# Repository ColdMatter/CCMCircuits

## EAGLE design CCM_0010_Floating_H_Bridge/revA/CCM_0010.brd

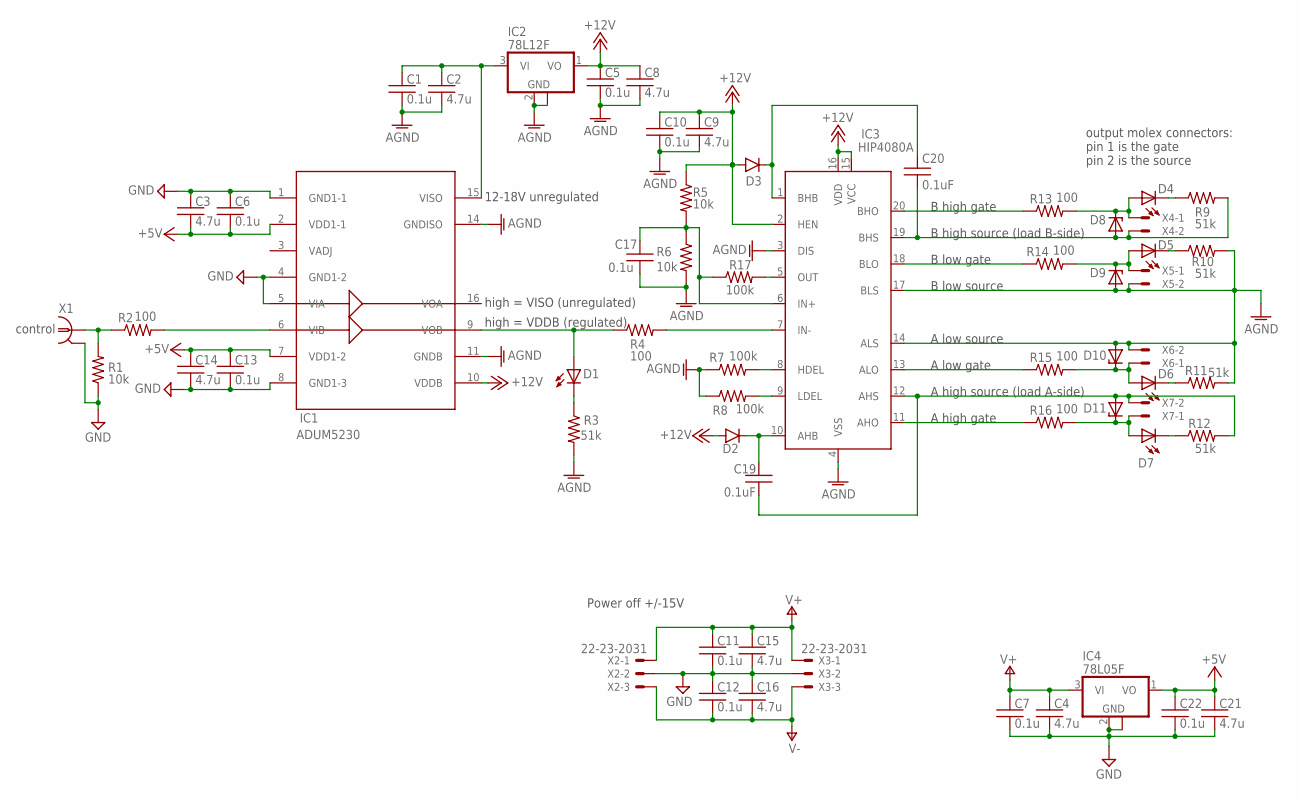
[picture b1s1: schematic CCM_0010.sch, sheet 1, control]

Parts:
C1, C5, C6, C7, C10, C11, C12, C13, C17, C22: 0.1u; 0603
C2, C3, C4, C8, C9, C14, C15, C16, C21: 4.7u; 0603
C19, C20: 0.1uF; 0603
D1, D4, D5, D6, D7: LED0603
D2, D3: DIODESOT23; SOT23-3
D8, D9, D10, D11: ZENER-DIODESOT23; SOT23
IC1: ADUM5230; SO16W
IC2: 78L12F; SOT89
IC3: HIP4080A; SO20W
IC4: 78L05F; SOT89
R1, R5, R6: 10k; 0603
R2, R4, R13, R14, R15, R16: 100; 0603
R3, R9, R10, R11, R12: 51k; 0603
R7, R8, R17: 100k; 0603
X1: 1-227161-0; AMP_227161
X2, X3: 22-23-2031
X4, X5, X6, X7: 22-23-2021

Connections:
+5V: C3.2, C6.2, C13.1, C14.1, C21.1, C22.1, IC1.2 (VDD1-1), IC1.7 (VDD1-2), IC4.1 (VO)
+12V: C5.1, C8.1, C9.1, C10.1, D2.1 (A), D3.1 (A), IC1.10 (VDDB), IC2.1 (VO), IC3.2 (HEN), IC3.15 (VCC), IC3.16 (VDD), R5.1
AGND: C1.2, C2.2, C5.2, C8.2, C9.2, C10.2, C17.2, D9.1 (A), D10.1 (A), IC1.11 (GNDB), IC1.14 (GNDISO), IC2.2 (GND), IC2.2@1 (GND), IC3.3 (DIS), IC3.4 (VSS), IC3.14 (ALS), IC3.17 (BLS), R3.2, R6.2, R7.1, R8.1, R10.2, R11.2, X5.2, X6.2
GND: C3.1, C4.2, C6.1, C7.2, C11.2, C12.1, C13.2, C14.2, C15.2, C16.1, C21.2, C22.2, IC1.1 (GND1-1), IC1.4 (GND1-2), IC1.5 (VIA), IC1.8 (GND1-3), IC4.2 (GND), IC4.2@1 (GND), R1.1, X1.2, X2.2, X3.2
unnamed: D1.C, R3.1
unnamed: D4.C, R9.1
unnamed: D5.C, R10.1
unnamed: IC3.20 (BHO), R13.1
unnamed: D5.A, D9.3 (C), R14.2, X5.1
unnamed: D6.C, R11.1
unnamed: D4.A, D8.3 (C), R13.2, X4.1
unnamed: D1.A, IC1.9 (VOB), R4.1
unnamed: D7.C, R12.1
unnamed: C1.1, C2.1, IC1.15 (VISO), IC2.3 (VI)
unnamed: IC3.11 (AHO), R16.1
unnamed: IC3.13 (ALO), R15.1
unnamed: IC3.7 (IN-), R4.2
unnamed: IC3.9 (LDEL), R8.2
unnamed: C20.2, D3.3 (C), IC3.1 (BHB)
unnamed: C20.1, D8.1 (A), IC3.19 (BHS), R9.2, X4.2
unnamed: IC3.18 (BLO), R14.1
unnamed: IC3.5 (OUT), R17.2
unnamed: C19.1, D11.1 (A), IC3.12 (AHS), R12.2, X7.2
unnamed: D7.A, D11.3 (C), R16.2, X7.1
unnamed: C19.2, D2.3 (C), IC3.10 (AHB)
unnamed: IC3.8 (HDEL), R7.2
unnamed: D6.A, D10.3 (C), R15.2, X6.1
unnamed: R1.2, R2.1, X1.1
unnamed: C17.1, IC3.6 (IN+), R5.2, R6.1, R17.1
unnamed: IC1.6 (VIB), R2.2
V+: C4.1, C7.1, C11.1, C15.1, IC4.3 (VI), X2.1, X3.1
V-: C12.2, C16.2, X2.3, X3.3

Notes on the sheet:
B high source (load B-side)
B high gate
B low gate
B low source
A high gate
A high source (load A-side)
A low gate
A low source
control
12-18V unregulated
high = VISO (unregulated)
high = VDDB (regulated)
Power off +/-15V
output molex connectors: pin 1 is the gate pin 2 is the source

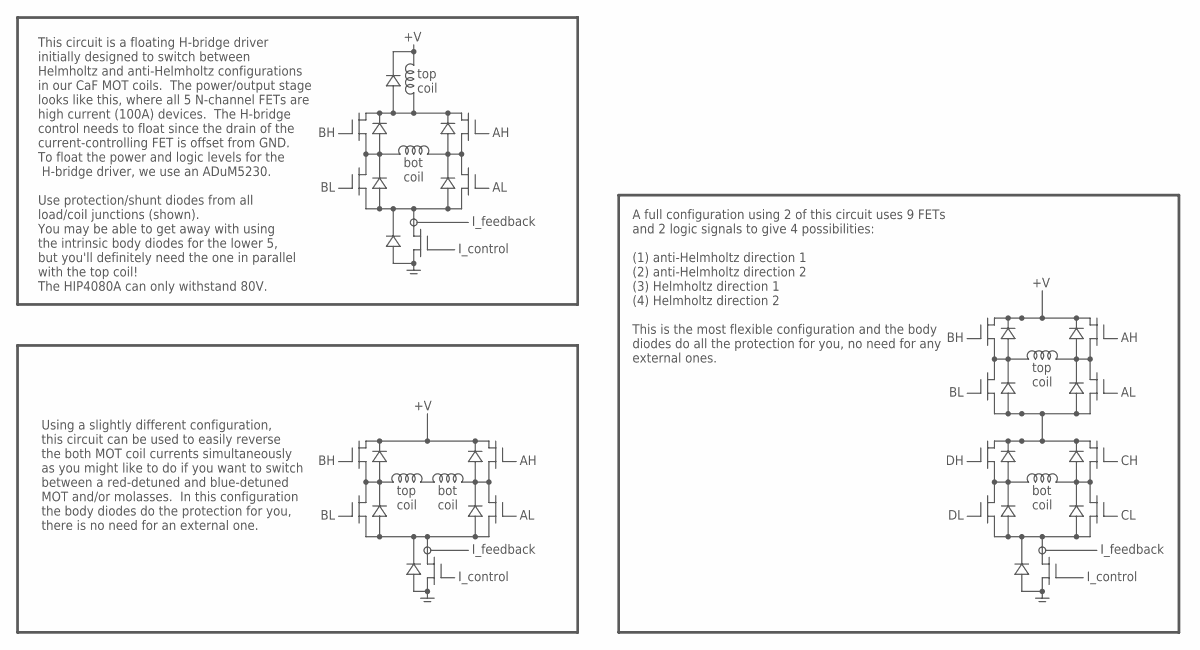
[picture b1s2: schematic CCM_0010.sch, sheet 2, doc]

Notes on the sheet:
I_control
top coil
bot coil
This circuit is a floating H-bridge driver initially designed to switch between Helmholtz and anti-Helmholtz configurations in our CaF MOT coils. The power/output stage looks like this, where all 5 N-channel FETs are high current (100A) devices. The H-bridge control needs to float since the drain o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
I_feedback
Using a slightly different configuration, this circuit can be used to easily reverse the both MOT coil currents simultaneously as you might like to do if you want to switch between a red-detuned and blue-detuned MOT and/or molasses. In this configuration the body diodes do the protection for you, t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
A full configuration using 2 of this circuit uses 9 FETs and 2 logic signals to give 4 possibilities: (1) anti-Helmholtz direction 1 (2) anti-Helmholtz direction 2 (3) Helmholtz direction 1 (4) Helmholtz direction 2 This is the most flexible configuration and the body diodes do all the protection f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

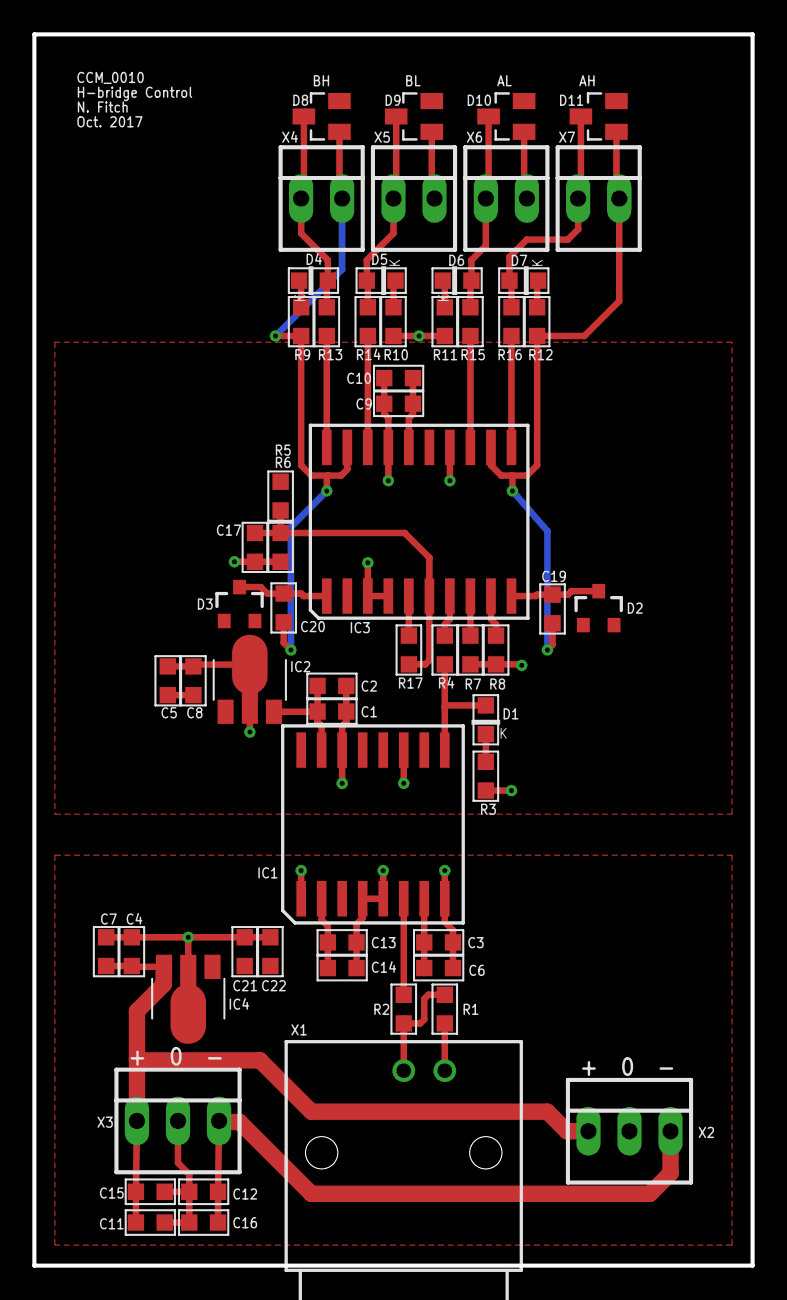
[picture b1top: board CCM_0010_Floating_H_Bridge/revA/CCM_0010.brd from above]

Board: 2 copper layers, 44.5 x 76.2 mm, 60 parts (0 on the bottom side), 32 nets.

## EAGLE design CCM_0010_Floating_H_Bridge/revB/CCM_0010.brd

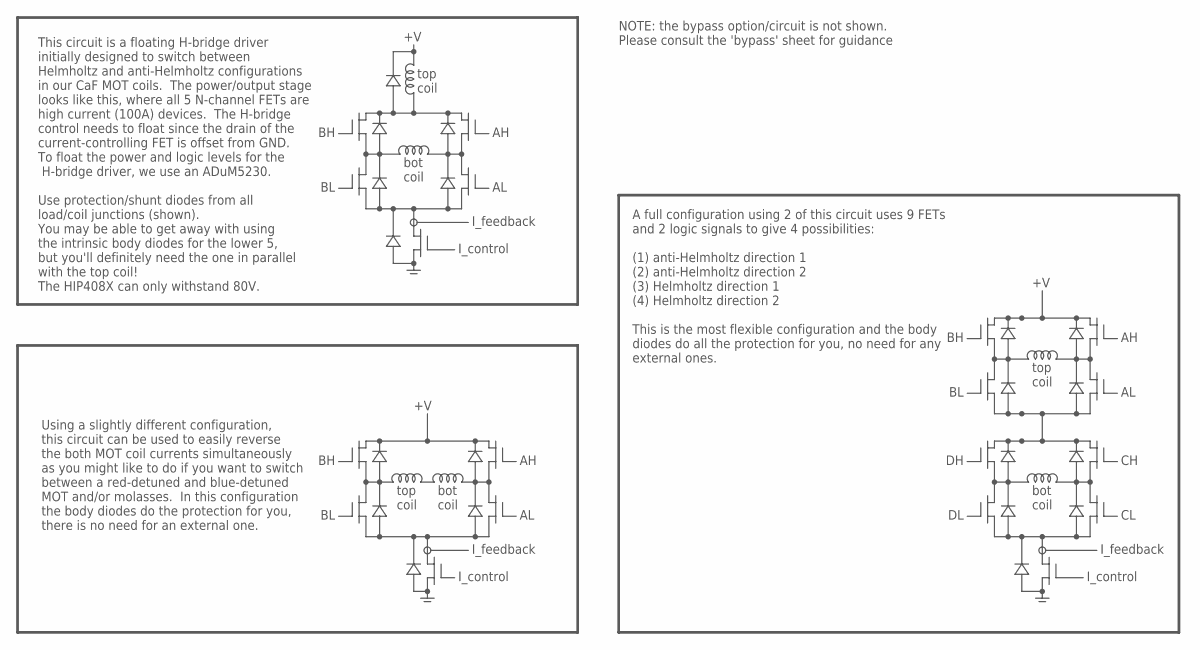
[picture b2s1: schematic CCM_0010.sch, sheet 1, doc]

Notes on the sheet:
I_control
top coil
bot coil
This circuit is a floating H-bridge driver initially designed to switch between Helmholtz and anti-Helmholtz configurations in our CaF MOT coils. The power/output stage looks like this, where all 5 N-channel FETs are high current (100A) devices. The H-bridge control needs to float since the drain o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
I_feedback
Using a slightly different configuration, this circuit can be used to easily reverse the both MOT coil currents simultaneously as you might like to do if you want to switch between a red-detuned and blue-detuned MOT and/or molasses. In this configuration the body diodes do the protection for you, t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
A full configuration using 2 of this circuit uses 9 FETs and 2 logic signals to give 4 possibilities: (1) anti-Helmholtz direction 1 (2) anti-Helmholtz direction 2 (3) Helmholtz direction 1 (4) Helmholtz direction 2 This is the most flexible configuration and the body diodes do all the protection f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
NOTE: the bypass option/circuit is not shown. Please consult the 'bypass' sheet for guidance

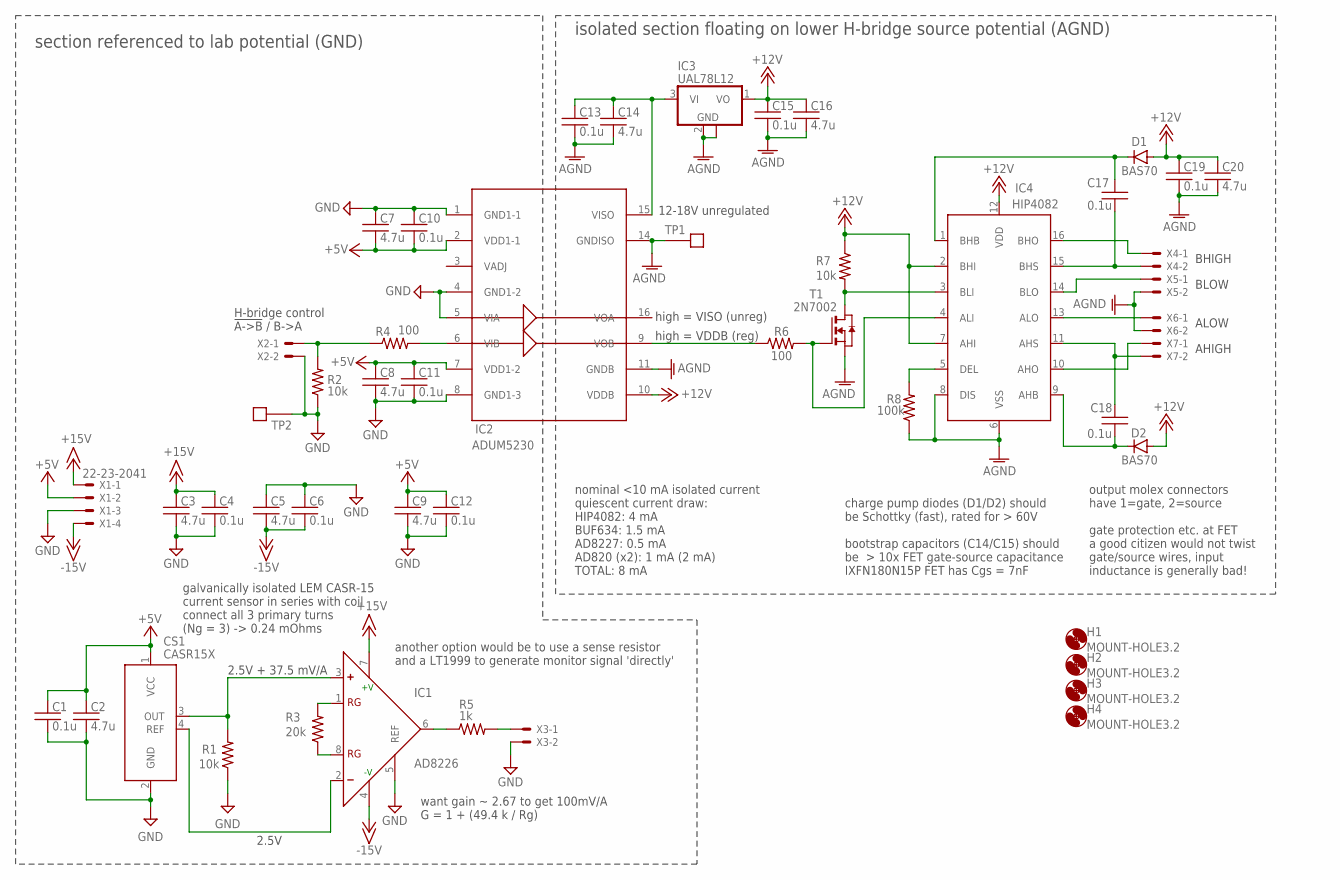
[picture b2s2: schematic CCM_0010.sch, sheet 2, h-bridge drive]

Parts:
C1, C4, C6, C10, C11, C12, C13, C15, C17, C18, C19: 0.1u; 0603
C2, C3, C5, C7, C8, C9, C14, C16, C20: 4.7u; 0603
CS1: CASR15X; 22-23-2041
D1, D2: BAS70; SOT23-3
H1, H2, H3, H4: MOUNT-HOLE3.2; 3,2
IC1: AD8226; SO8
IC2: ADUM5230; SO16W
IC3: UAL78L12; SOT89
IC4: HIP4082; SO16
R1, R2, R7: 10k; 0603
R3: 20k; 0603
R4, R6: 100; 0603
R5: 1k; 0603
R8: 100k; 0603
T1: 2N7002; SOT-23
TP1, TP2: TESTPOINT
X1: 22-23-2041
X2, X3, X4, X5, X6, X7: 22-23-2021

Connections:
+5V: C1.1, C2.1, C7.2, C8.1, C9.1, C10.2, C11.1, C12.1, CS1.1 (VCC), IC2.2 (VDD1-1), IC2.7 (VDD1-2), X1.2
+12V: C15.1, C16.1, C19.1, C20.1, D1.1 (A), D2.1 (A), IC2.10 (VDDB), IC3.1 (VO), IC4.2 (BHI), IC4.7 (AHI), IC4.12 (VDD), R7.1; also elsewhere on the board
+15V: C3.1, C4.1, IC1.7 (+V), X1.1; also elsewhere on the board
-15V: C5.2, C6.2, IC1.4 (-V), X1.4; also elsewhere on the board
AGND: C13.2, C14.2, C15.2, C16.2, C19.2, C20.2, IC2.11 (GNDB), IC2.14 (GNDISO), IC3.2 (GND), IC3.2@1 (GND), IC4.6 (VSS), IC4.8 (DIS), R8.1, T1.2 (S), TP1.P$1, X5.2, X6.2; also elsewhere on the board
GND: C1.2, C2.2, C3.2, C4.2, C5.1, C6.1, C7.1, C8.2, C9.2, C10.1, C11.2, C12.2, CS1.2 (GND), IC1.5 (REF), IC2.1 (GND1-1), IC2.4 (GND1-2), IC2.5 (VIA), IC2.8 (GND1-3), R1.1, R2.1, TP2.P$1, X1.3, X2.2, X3.2; also elsewhere on the board
unnamed: IC4.5 (DEL), R8.2
unnamed: C13.1, C14.1, IC2.15 (VISO), IC3.3 (VI)
unnamed: IC2.9 (VOB), R6.1
unnamed: C18.2, IC4.11 (AHS), X7.2
unnamed: C17.2, D1.3 (C), IC4.1 (BHB)
unnamed: C18.1, D2.3 (C), IC4.9 (AHB)
unnamed: IC4.3 (BLI), R7.2, T1.1 (D)
unnamed: IC4.4 (ALI), R6.2, T1.3 (G)
unnamed: C17.1, IC4.15 (BHS), X4.2
unnamed: IC4.16 (BHO), X4.1
unnamed: R2.2, R4.1, X2.1
unnamed: IC4.14 (BLO), X5.1
unnamed: IC2.6 (VIB), R4.2
unnamed: IC4.13 (ALO), X6.1
unnamed: IC4.10 (AHO), X7.1
unnamed: IC1.6 (OUT), R5.1
unnamed: IC1.1 (RG), R3.2
unnamed: IC1.8 (RG), R3.1
unnamed: CS1.3 (OUT), IC1.3 (+), R1.2
unnamed: CS1.4 (REF), IC1.2 (-)
unnamed: R5.2, X3.1

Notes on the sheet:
H-bridge control !A->B! / B->A
12-18V unregulated
high = VISO (unreg)
high = VDDB (reg)
output molex connectors have 1=gate, 2=source gate protection etc. at FET a good citizen would not twist gate/source wires, input inductance is generally bad!
charge pump diodes (D1/D2) should be Schottky (fast), rated for > 60V bootstrap capacitors (C14/C15) should be > 10x FET gate-source capacitance IXFN180N15P FET has Cgs = 7nF
nominal <10 mA isolated current quiescent current draw: HIP4082: 4 mA BUF634: 1.5 mA AD8227: 0.5 mA AD820 (x2): 1 mA (2 mA) TOTAL: 8 mA
BHIGH
BLOW
ALOW
AHIGH
2.5V
galvanically isolated LEM CASR-15 current sensor in series with coil connect all 3 primary turns (Ng = 3) -> 0.24 mOhms
want gain ~ 2.67 to get 100mV/A G = 1 + (49.4 k / Rg)
isolated section floating on lower H-bridge source potential (AGND)
section referenced to lab potential (GND)
another option would be to use a sense resistor and a LT1999 to generate monitor signal 'directly'
2.5V + 37.5 mV/A

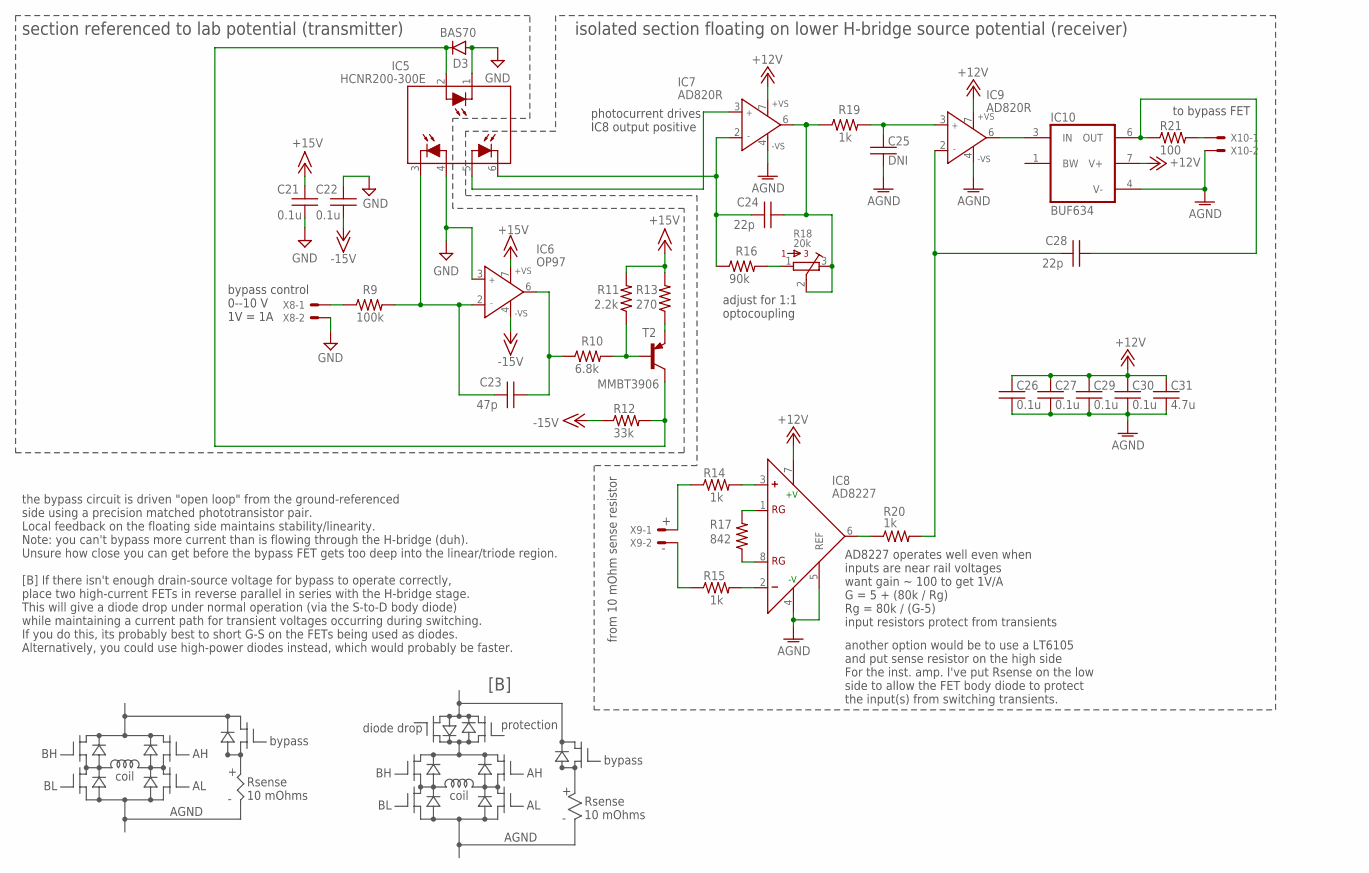
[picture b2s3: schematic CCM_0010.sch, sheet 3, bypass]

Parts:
C21, C22, C26, C27, C29, C30: 0.1u; 0603
C23: 47p; 0603
C24, C28: 22p; 0603
C25: DNI; 0603
C31: 4.7u; 0603
D3: BAS70; SOT23-3
IC5: HCNR200-300E; DIP8-400
IC6: OP97; SO8
IC7, IC9: AD820R; SO8
IC8: AD8227; SO8
IC10: BUF634; SO8
R9: 100k; 0603
R10: 6.8k; 0603
R11: 2.2k; 0603
R12: 33k; 0603
R13: 270; 0603
R14, R15, R19, R20: 1k; 0603
R16: 90k; 0603
R17: 842; 0603
R18: 20k; 3386W
R21: 100; 0603
T2: MMBT3906; SOT23-BEC
X8, X9, X10: 22-23-2021

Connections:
+12V: C26.1, C27.1, C29.1, C30.1, C31.1, IC7.7 (+VS), IC8.7 (+V), IC9.7 (+VS), IC10.7 (V+); also elsewhere on the board
+15V: C21.2, IC6.7 (+VS), R11.2, R13.2; also elsewhere on the board
-15V: C22.1, IC6.4 (-VS), R12.1; also elsewhere on the board
AGND: C25.2, C26.2, C27.2, C29.2, C30.2, C31.2, IC7.4 (-VS), IC8.4 (-V), IC8.5 (REF), IC9.4 (-VS), IC10.4 (V-), X10.2; also elsewhere on the board
GND: C21.1, C22.2, D3.1 (A), IC5.1 (C), IC5.4 (A1), IC6.3 (IN+), X8.2; also elsewhere on the board
unnamed: D3.3 (C), IC5.2 (A), R12.2, T2.C
unnamed: C24.1, IC7.6 (OUT), R18.2, R18.3, R19.1
unnamed: R9.1, X8.1
unnamed: C23.2, IC5.3 (C1), IC6.2 (IN-), R9.2
unnamed: R16.2, R18.1
unnamed: C23.1, IC6.6 (OUT), R10.1
unnamed: R10.2, R11.1, T2.B
unnamed: R13.1, T2.E
unnamed: C24.2, IC5.6 (C2), IC7.2 (IN-), R16.1
unnamed: IC5.5 (A2), IC7.3 (IN+)
unnamed: IC9.6 (OUT), IC10.3 (IN)
unnamed: C28.1, IC10.6 (OUT), R21.1
unnamed: R21.2, X10.1
unnamed: C28.2, IC9.2 (IN-), R20.2
unnamed: IC8.6 (OUT), R20.1
unnamed: IC8.1 (RG), R17.2
unnamed: IC8.8 (RG), R17.1
unnamed: C25.1, IC9.3 (IN+), R19.2
unnamed: R14.1, X9.1
unnamed: R15.1, X9.2
unnamed: IC8.2 (-), R15.2
unnamed: IC8.3 (+), R14.2

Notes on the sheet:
isolated section floating on lower H-bridge source potential (receiver)
section referenced to lab potential (transmitter)
adjust for 1:1 optocoupling
AD8227 operates well even when inputs are near rail voltages want gain ~ 100 to get 1V/A G = 5 + (80k / Rg) Rg = 80k / (G-5) input resistors protect from transients
from 10 mOhm sense resistor
to bypass FET
bypass control 0--10 V 1V = 1A
photocurrent drives IC8 output positive
the bypass circuit is driven "open loop" from the ground-referenced side using a precision matched phototransistor pair. Local feedback on the floating side maintains stability/linearity. Note: you can't bypass more current than is flowing through the H-bridge (duh). Unsure how close you can get be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
coil
bypass
Rsense 10 mOhms
+ -
AGND
[B]
protection
diode drop
another option would be to use a LT6105 and put sense resistor on the high side For the inst. amp. I've put Rsense on the low side to allow the FET body diode to protect the input(s) from switching transients.

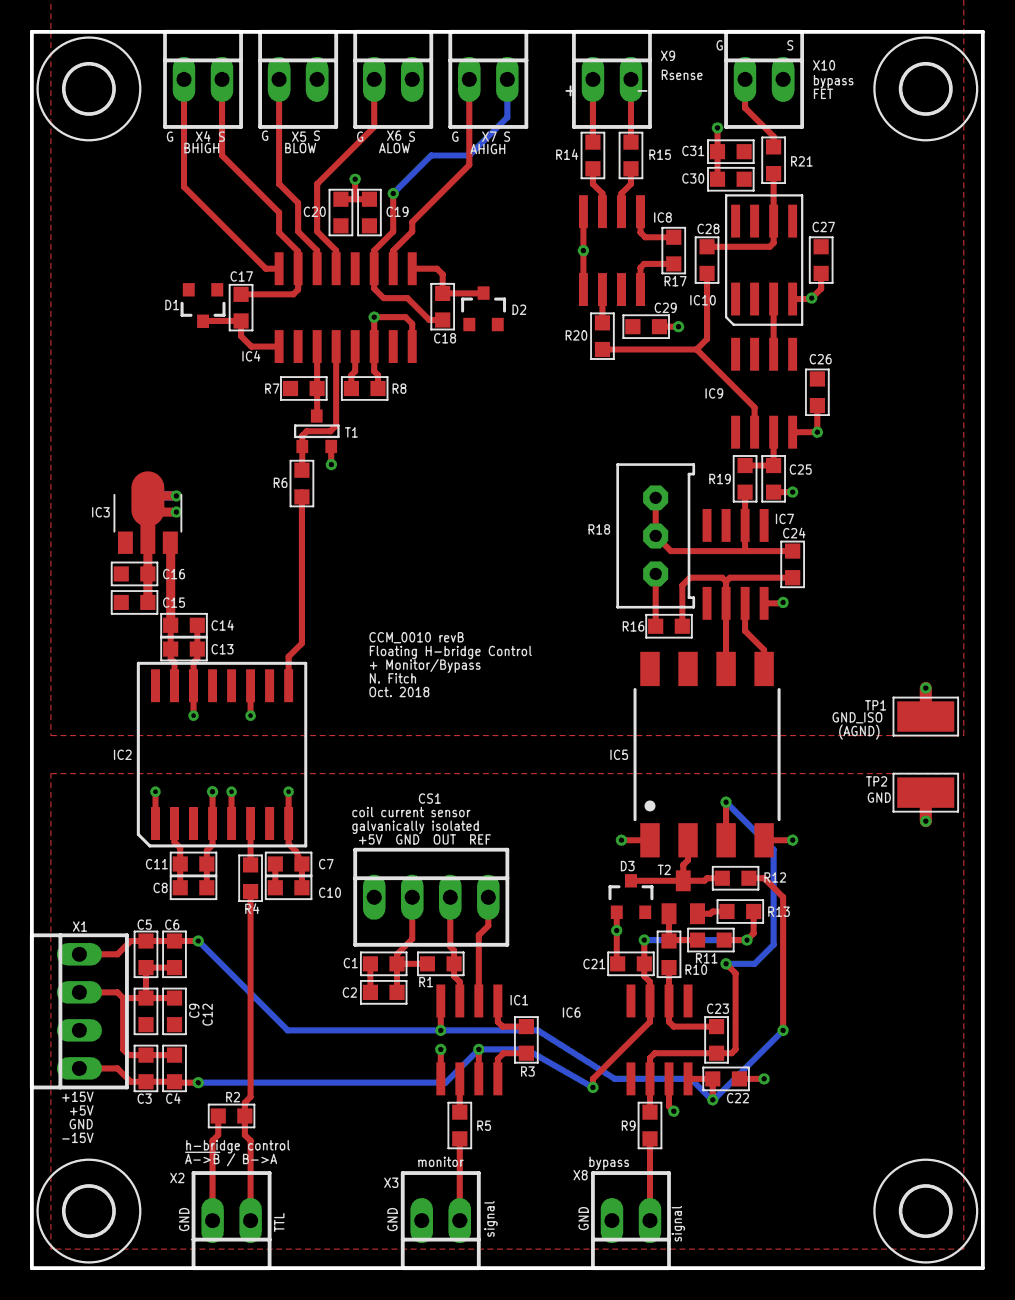
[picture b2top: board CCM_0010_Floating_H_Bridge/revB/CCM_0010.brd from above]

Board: 2 copper layers, 63.5 x 82.5 mm, 84 parts (0 on the bottom side), 49 nets.

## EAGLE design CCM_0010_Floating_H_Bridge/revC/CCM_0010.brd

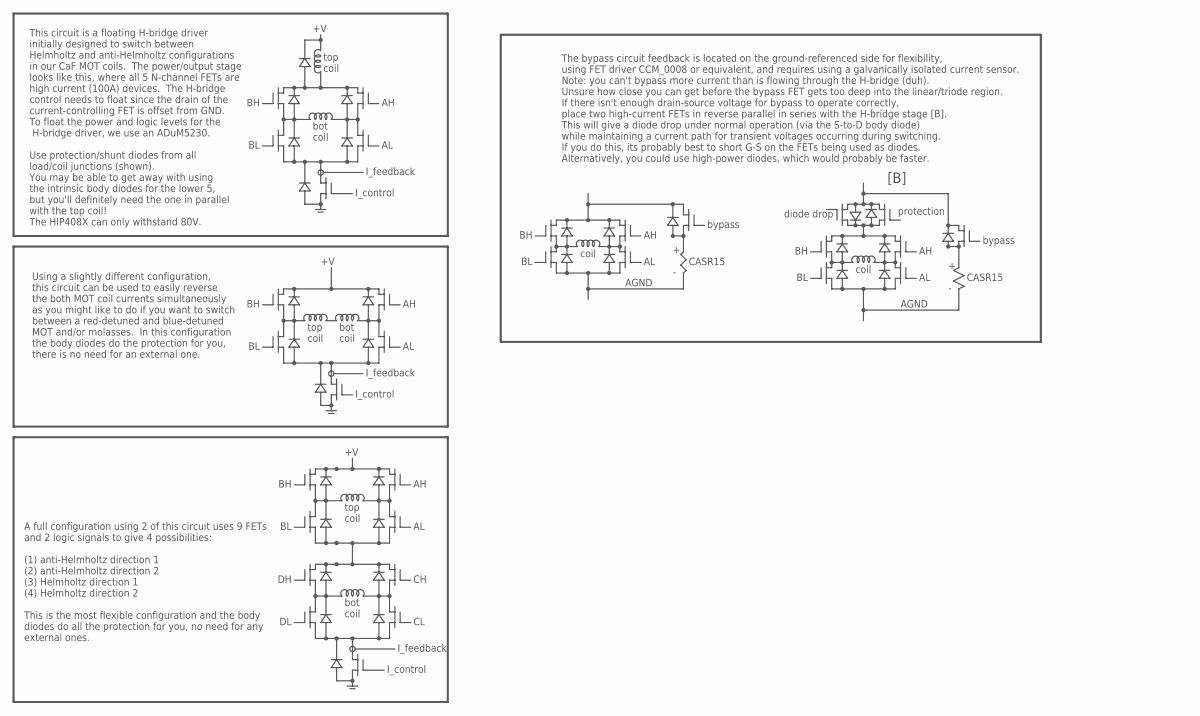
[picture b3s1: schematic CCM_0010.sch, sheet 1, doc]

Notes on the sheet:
I_control
top coil
bot coil
This circuit is a floating H-bridge driver initially designed to switch between Helmholtz and anti-Helmholtz configurations in our CaF MOT coils. The power/output stage looks like this, where all 5 N-channel FETs are high current (100A) devices. The H-bridge control needs to float since the drain o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
I_feedback
Using a slightly different configuration, this circuit can be used to easily reverse the both MOT coil currents simultaneously as you might like to do if you want to switch between a red-detuned and blue-detuned MOT and/or molasses. In this configuration the body diodes do the protection for you, t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
A full configuration using 2 of this circuit uses 9 FETs and 2 logic signals to give 4 possibilities: (1) anti-Helmholtz direction 1 (2) anti-Helmholtz direction 2 (3) Helmholtz direction 1 (4) Helmholtz direction 2 This is the most flexible configuration and the body diodes do all the protection f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
The bypass circuit feedback is located on the ground-referenced side for flexibility, using FET driver CCM_0008 or equivalent, and requires using a galvanically isolated current sensor. Note: you can't bypass more current than is flowing through the H-bridge (duh). Unsure how close you can get befo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
coil
bypass
CASR15
+ -
AGND
[B]
protection
diode drop

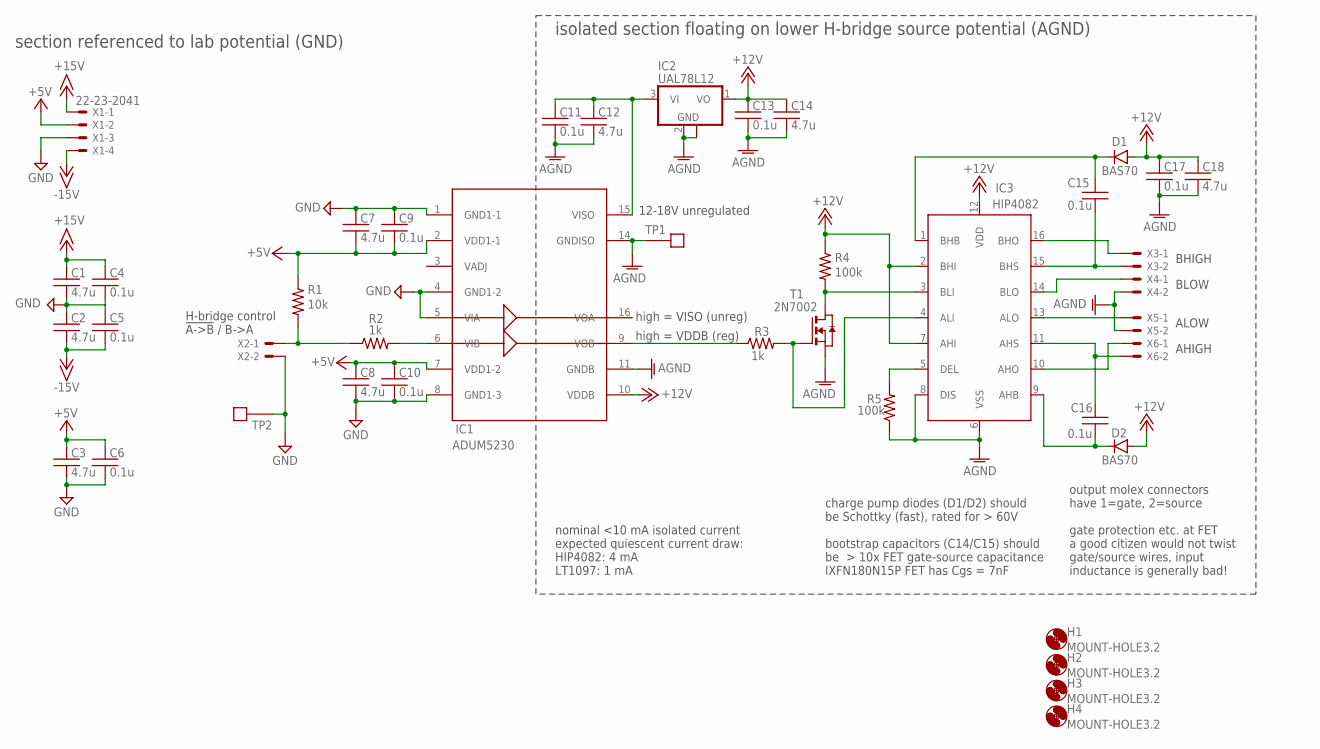
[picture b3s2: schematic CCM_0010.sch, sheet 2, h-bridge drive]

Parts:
C1, C2, C3, C7, C8, C12, C14, C18: 4.7u; 0603
C4, C5, C6, C9, C10, C11, C13, C15, C16, C17: 0.1u; 0603
D1, D2: BAS70; SOT23-3
H1, H2, H3, H4: MOUNT-HOLE3.2; 3,2
IC1: ADUM5230; SO16W
IC2: UAL78L12; SOT89
IC3: HIP4082; SO16
R1: 10k; 0603
R2, R3: 1k; 0603
R4, R5: 100k; 0603
T1: 2N7002; SOT-23
TP1, TP2: TESTPOINT
X1: 22-23-2041
X2, X3, X4, X5, X6: 22-23-2021

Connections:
+5V: C3.1, C6.1, C7.2, C8.1, C9.2, C10.1, IC1.2 (VDD1-1), IC1.7 (VDD1-2), R1.1, X1.2
+12V: C13.1, C14.1, C17.1, C18.1, D1.1 (A), D2.1 (A), IC1.10 (VDDB), IC2.1 (VO), IC3.2 (BHI), IC3.7 (AHI), IC3.12 (VDD), R4.1; also elsewhere on the board
+15V: C1.1, C4.1, X1.1; also elsewhere on the board
-15V: C2.2, C5.2, X1.4; also elsewhere on the board
AGND: C11.2, C12.2, C13.2, C14.2, C17.2, C18.2, IC1.11 (GNDB), IC1.14 (GNDISO), IC2.2 (GND), IC2.2@1 (GND), IC3.6 (VSS), IC3.8 (DIS), R5.1, T1.2 (S), TP1.P$1, X4.2, X5.2; also elsewhere on the board
GND: C1.2, C2.1, C3.2, C4.2, C5.1, C6.2, C7.1, C8.2, C9.1, C10.2, IC1.1 (GND1-1), IC1.4 (GND1-2), IC1.5 (VIA), IC1.8 (GND1-3), TP2.P$1, X1.3, X2.2; also elsewhere on the board
unnamed: IC3.5 (DEL), R5.2
unnamed: C11.1, C12.1, IC1.15 (VISO), IC2.3 (VI)
unnamed: IC1.9 (VOB), R3.1
unnamed: C16.2, IC3.11 (AHS), X6.2
unnamed: C15.2, D1.3 (C), IC3.1 (BHB)
unnamed: C16.1, D2.3 (C), IC3.9 (AHB)
unnamed: IC3.3 (BLI), R4.2, T1.1 (D)
unnamed: IC3.4 (ALI), R3.2, T1.3 (G)
unnamed: C15.1, IC3.15 (BHS), X3.2
unnamed: IC3.16 (BHO), X3.1
unnamed: R1.2, R2.1, X2.1
unnamed: IC3.14 (BLO), X4.1
unnamed: IC1.6 (VIB), R2.2
unnamed: IC3.13 (ALO), X5.1
unnamed: IC3.10 (AHO), X6.1

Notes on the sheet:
H-bridge control !A->B! / B->A
12-18V unregulated
high = VISO (unreg)
high = VDDB (reg)
output molex connectors have 1=gate, 2=source gate protection etc. at FET a good citizen would not twist gate/source wires, input inductance is generally bad!
charge pump diodes (D1/D2) should be Schottky (fast), rated for > 60V bootstrap capacitors (C14/C15) should be > 10x FET gate-source capacitance IXFN180N15P FET has Cgs = 7nF
nominal <10 mA isolated current expected quiescent current draw: HIP4082: 4 mA LT1097: 1 mA
BHIGH
BLOW
ALOW
AHIGH
isolated section floating on lower H-bridge source potential (AGND)
section referenced to lab potential (GND)

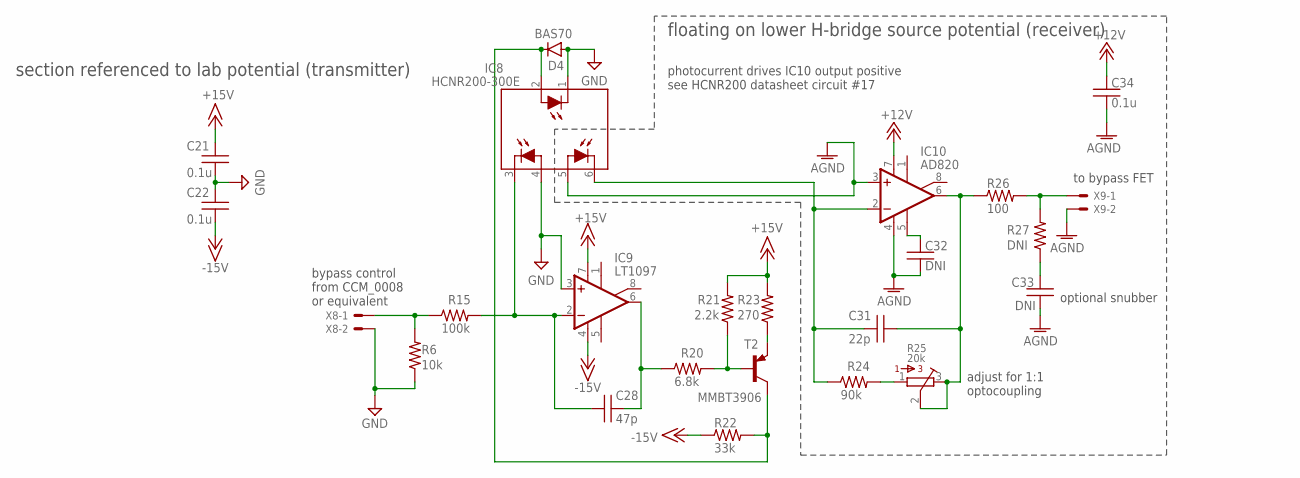
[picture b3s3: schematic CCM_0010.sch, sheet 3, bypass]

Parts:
C21, C22, C34: 0.1u; 0603
C28: 47p; 0603
C31: 22p; 0603
C32, C33: DNI; 0603
D4: BAS70; SOT23-3
IC8: HCNR200-300E; DIP8-400
IC9: LT1097; SO08
IC10: AD820; SO08
R6: 10k; 0603
R15: 100k; 0603
R20: 6.8k; 0603
R21: 2.2k; 0603
R22: 33k; 0603
R23: 270; 0603
R24: 90k; 0603
R25: 20k; 3386W
R26: 100; 0603
R27: DNI; 0603
T2: MMBT3906; SOT23-BEC
X8, X9: 22-23-2021

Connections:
+12V: C34.1, IC10.7 (V+); also elsewhere on the board
+15V: C21.2, IC9.7 (V+), R21.2, R23.2; also elsewhere on the board
-15V: C22.1, IC9.4 (V-), R22.1; also elsewhere on the board
AGND: C32.2, C33.2, C34.2, IC8.5 (A2), IC10.3 (+IN), IC10.4 (V-), X9.2; also elsewhere on the board
GND: C21.1, C22.2, D4.1 (A), IC8.1 (C), IC8.4 (A1), IC9.3 (+IN), R6.1, X8.2; also elsewhere on the board
unnamed: C32.1, IC10.5 (OPT)
unnamed: D4.3 (C), IC8.2 (A), R22.2, T2.C
unnamed: C33.1, R27.1
unnamed: R6.2, R15.1, X8.1
unnamed: C28.2, IC8.3 (C1), IC9.2 (-IN), R15.2
unnamed: R24.2, R25.1
unnamed: C28.1, IC9.6 (OUT), R20.1
unnamed: R20.2, R21.1, T2.B
unnamed: R23.1, T2.E
unnamed: C31.2, IC8.6 (C2), IC10.2 (-IN), R24.1
unnamed: C31.1, IC10.6 (OUT), R25.2, R25.3, R26.1
unnamed: R26.2, R27.2, X9.1

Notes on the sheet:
floating on lower H-bridge source potential (receiver)
section referenced to lab potential (transmitter)
adjust for 1:1 optocoupling
to bypass FET
bypass control from CCM_0008 or equivalent
photocurrent drives IC10 output positive see HCNR200 datasheet circuit #17
optional snubber

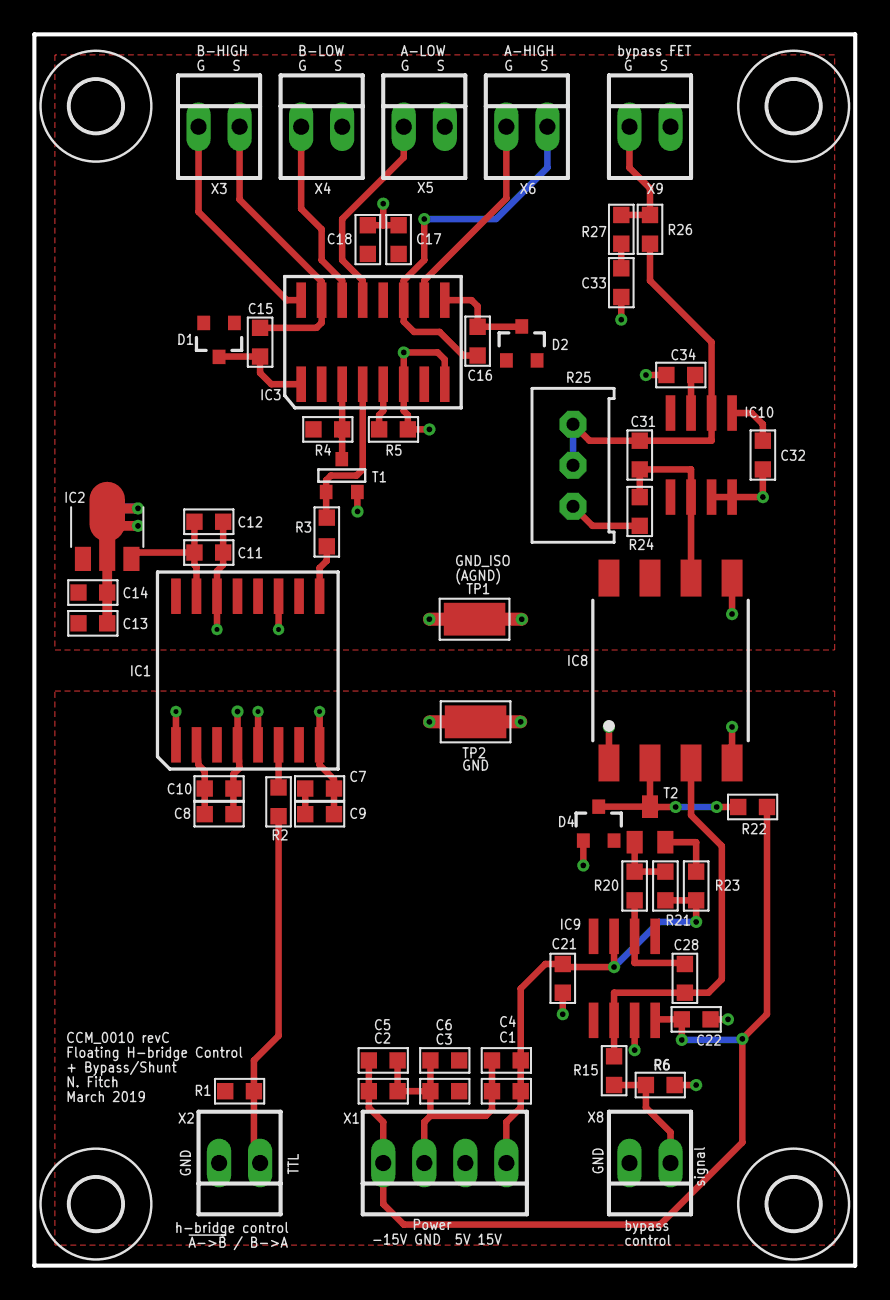
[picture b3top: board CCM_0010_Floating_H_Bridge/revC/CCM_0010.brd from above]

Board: 2 copper layers, 50.8 x 76.2 mm, 65 parts (0 on the bottom side), 33 nets.

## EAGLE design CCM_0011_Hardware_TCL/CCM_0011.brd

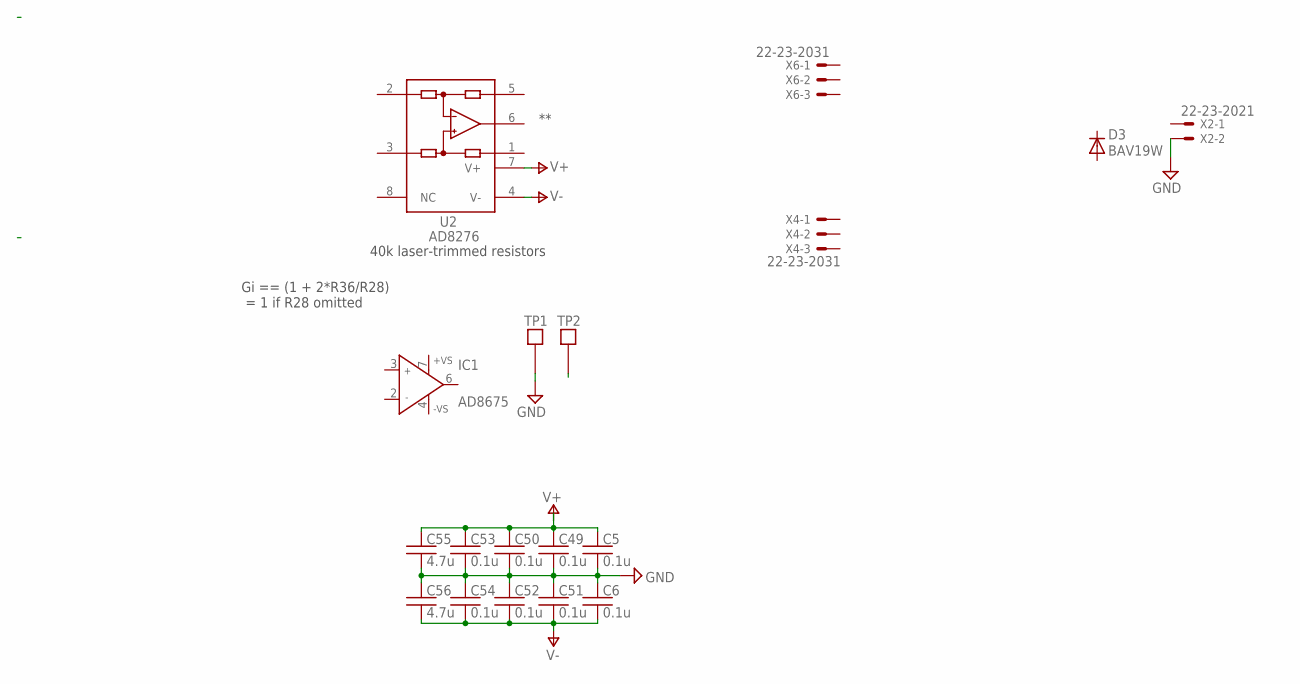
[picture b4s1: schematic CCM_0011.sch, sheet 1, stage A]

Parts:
C5, C6, C49, C50, C51, C52, C53, C54: 0.1u; 0603
C55, C56: 4.7u; 0603
D3: BAV19W; SOD123
IC1: AD8675; SO08
TP1, TP2: TESTPOINT
U2: AD8276; SO8
X2: 22-23-2021
X4, X6: 22-23-2031

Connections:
GND: C5.2, C6.1, C49.2, C50.2, C51.1, C52.1, C53.2, C54.1, C55.2, C56.1, TP1.P$1, X2.2; also elsewhere on the board
V+: C5.1, C49.1, C50.1, C53.1, C55.1, U2.7 (V+); also elsewhere on the board
V-: C6.2, C51.2, C52.2, C54.2, C56.2, U2.4 (V-); also elsewhere on the board

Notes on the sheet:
40k laser-trimmed resistors
Gi == (1 + 2*R36/R28) = 1 if R28 omitted

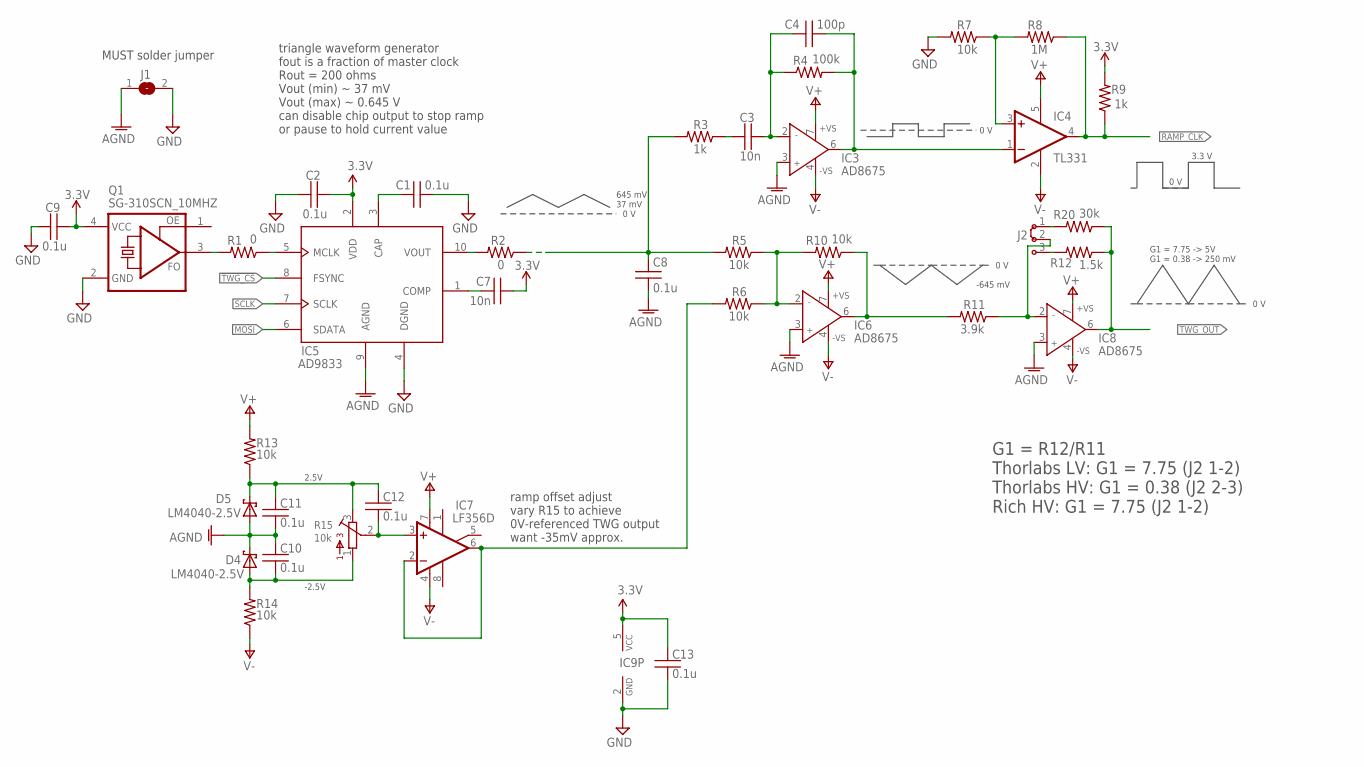
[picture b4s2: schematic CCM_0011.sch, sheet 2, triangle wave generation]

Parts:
C1, C2, C8, C9, C10, C11, C12, C13: 0.1u; 0603
C3, C7: 10n; 0603
C4: 100p; 0603
D4, D5: LM4040-2.5V; SOT23
IC3, IC6, IC8: AD8675; SO8
IC4: TL331; DBV-R-PDSO-G5
IC5: AD9833; MSOP10
IC7: LF356D; SO08
IC9: 741G3157DBVR; DBV_R-PDSO-G6
J1: SJ
J2: J2X2MM; 04C
Q1: SG-310SCN_10MHZ; ASF
R1, R2: 0; 0603
R3, R9: 1k; 0603
R4: 100k; 0603
R5, R6, R7, R10, R13, R14: 10k; 0603
R8: 1M; 0603
R11: 3.9k; 0603
R12: 1.5k; 0603
R15: 10k; 3386H
R20: 30k; 0603

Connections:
3.3V: C2.1, C7.1, C9.1, C13.1, IC5.2 (VDD), IC9.5 (VCC), Q1.4 (VCC), R9.2; also elsewhere on the board
!TWG_CS: IC5.8 (FSYNC)
AGND: C8.2, C10.1, C11.2, D4.1 (C), D5.2 (A), IC3.3 (IN+), IC5.9 (AGND), IC6.3 (IN+), IC8.3 (IN+), J1.1; also elsewhere on the board
GND: C1.1, C2.2, C9.2, C13.2, IC5.4 (DGND), IC9.2 (GND), J1.2, Q1.2 (GND), R7.2; also elsewhere on the board
MOSI: IC5.6 (SDATA)
unnamed: IC5.10 (VOUT), R2.2
unnamed: IC4.3 (+IN), R7.1, R8.2
unnamed: C1.2, IC5.3 (CAP)
unnamed: C3.1, R3.1
unnamed: C3.2, C4.2, IC3.2 (IN-), R4.1
unnamed: C4.1, IC3.6 (OUT), IC4.1 (-IN), R4.2
unnamed: C10.2, D4.2 (A), R14.2, R15.1
unnamed: C12.2, IC7.3 (+IN), R15.2
unnamed: IC7.2 (-IN), IC7.6 (OUT), R6.2
unnamed: IC6.2 (IN-), R5.1, R6.1, R10.2
unnamed: IC8.2 (IN-), J2.2, R11.1
unnamed: C11.1, C12.1, D5.1 (C), R13.1, R15.3
unnamed: IC6.6 (OUT), R10.1, R11.2
unnamed: Q1.3 (FO), R1.2
unnamed: C7.2, IC5.1 (COMP)
unnamed: IC5.5 (MCLK), R1.1
unnamed: J2.1, R20.2
unnamed: J2.3, R12.2
RAMP_CLK: IC4.4 (OUT), R8.1, R9.1
SCLK: IC5.7 (SCLK)
TWG_OUT: IC8.6 (OUT), R12.1, R20.1; also elsewhere on the board
TWG_RAW: C8.1, R2.1, R3.2, R5.2
V+: IC3.7 (+VS), IC4.5 (V+), IC6.7 (+VS), IC7.7 (V+), IC8.7 (+VS), R13.2; also elsewhere on the board
V-: IC3.4 (-VS), IC4.2 (GND), IC6.4 (-VS), IC7.4 (V-), IC8.4 (-VS), R14.1; also elsewhere on the board

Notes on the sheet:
triangle waveform generator fout is a fraction of master clock Rout = 200 ohms Vout (min) ~ 37 mV Vout (max) ~ 0.645 V can disable chip output to stop ramp or pause to hold current value
0 V
37 mV
645 mV
3.3 V
2.5V
-2.5V
ramp offset adjust vary R15 to achieve 0V-referenced TWG output want -35mV approx.
-645 mV
G1 = R12/R11 Thorlabs LV: G1 = 7.75 (J2 1-2) Thorlabs HV: G1 = 0.38 (J2 2-3) Rich HV: G1 = 7.75 (J2 1-2)
G1 = 7.75 -> 5V G1 = 0.38 -> 250 mV
MUST solder jumper
